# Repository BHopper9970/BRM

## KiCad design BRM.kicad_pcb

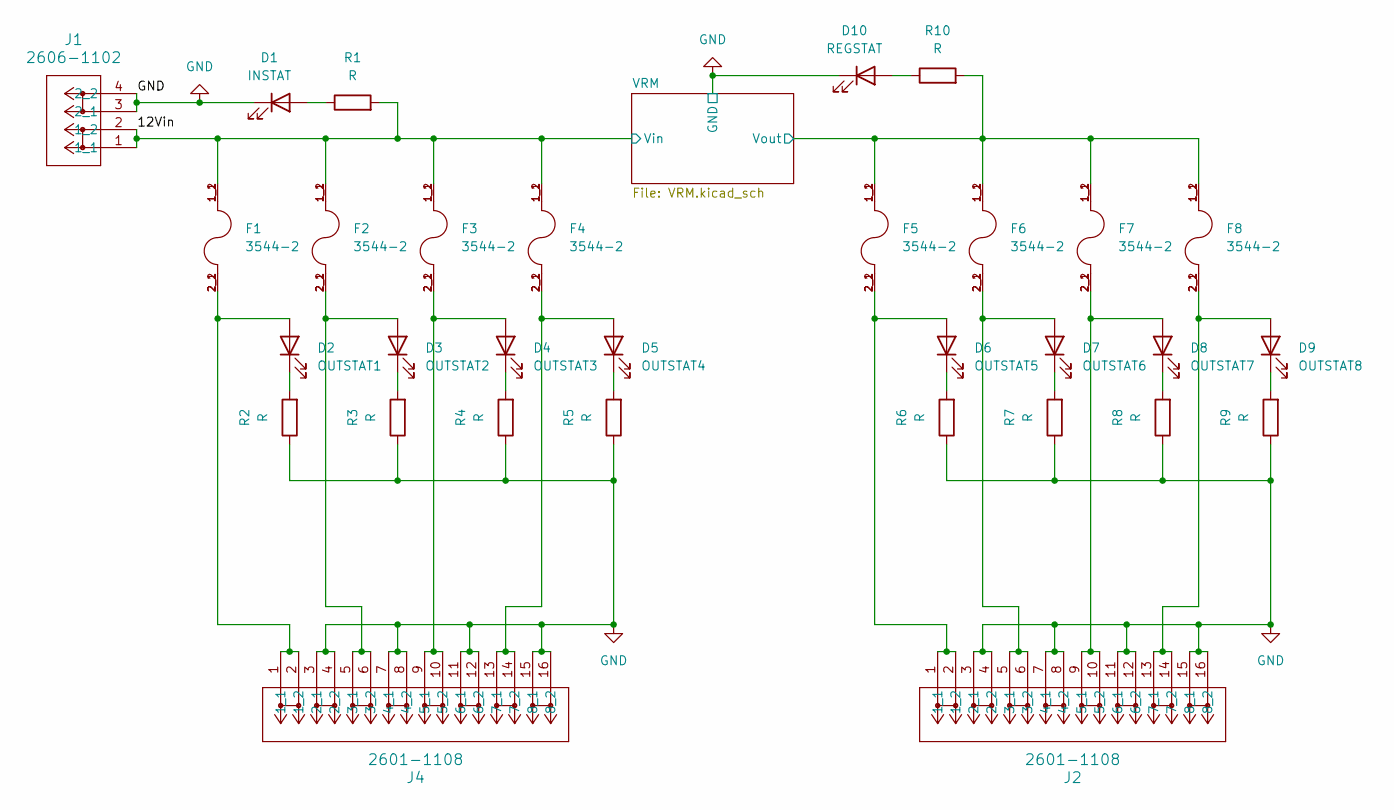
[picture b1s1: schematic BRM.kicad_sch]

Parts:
D1: INSTAT; LED_0805_2012Metric
D2: OUTSTAT1; LED_0805_2012Metric
D3: OUTSTAT2; LED_0805_2012Metric
D4: OUTSTAT3; LED_0805_2012Metric
D5: OUTSTAT4; LED_0805_2012Metric
D6: OUTSTAT5; LED_0805_2012Metric
D7: OUTSTAT6; LED_0805_2012Metric
D8: OUTSTAT7; LED_0805_2012Metric
D9: OUTSTAT8; LED_0805_2012Metric
D10: REGSTAT; LED_0805_2012Metric
F1, F2, F3, F4, F5, F6, F7, F8: 3544-2; FUSE_3544-2; PARTREV C
J1: 2606-1102; CONN2_2606-1102_WAG
J2, J4: 2601-1108; CONN8_2601-1108_WAG
R1, R2, R3, R4, R5, R6, R7, R8, R9, R10: R; R_0603_1608Metric

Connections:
/12Vin: F1.1_1, F1.1_2, F2.1_1, F2.1_2, F3.1_1, F3.1_2, F4.1_1, F4.1_2, J1.1 (1_1), J1.2 (1_2), R1.2; also elsewhere on the board
/VRM/Vout: F5.1_1, F5.1_2, F6.1_1, F6.1_2, F7.1_1, F7.1_2, F8.1_1, F8.1_2, R10.2; also elsewhere on the board
GND: D1.1 (K), D10.1 (K), J1.3 (2_1), J1.4 (2_2), J2.3 (2_1), J2.4 (2_2), J2.7 (4_1), J2.8 (4_2), J2.11 (6_1), J2.12 (6_2), J2.15 (8_1), J2.16 (8_2), J4.3 (2_1), J4.4 (2_2), J4.7 (4_1), J4.8 (4_2), J4.11 (6_1), J4.12 (6_2), J4.15 (8_1), J4.16 (8_2), R2.1, R3.1, R4.1, R5.1, R6.1, R7.1, R8.1, R9.1; also elsewhere on the board
unnamed: D1.2 (A), R1.1
unnamed: D2.2 (A), F1.2_1, F1.2_2, J4.1 (1_1), J4.2 (1_2)
unnamed: D2.1 (K), R2.2
unnamed: D3.2 (A), F2.2_1, F2.2_2, J4.5 (3_1), J4.6 (3_2)
unnamed: D3.1 (K), R3.2
unnamed: D4.2 (A), F3.2_1, F3.2_2, J4.9 (5_1), J4.10 (5_2)
unnamed: D4.1 (K), R4.2
unnamed: D5.2 (A), F4.2_1, F4.2_2, J4.13 (7_1), J4.14 (7_2)
unnamed: D5.1 (K), R5.2
unnamed: D6.2 (A), F5.2_1, F5.2_2, J2.1 (1_1), J2.2 (1_2)
unnamed: D6.1 (K), R6.2
unnamed: D7.2 (A), F6.2_1, F6.2_2, J2.5 (3_1), J2.6 (3_2)
unnamed: D7.1 (K), R7.2
unnamed: D8.2 (A), F7.2_1, F7.2_2, J2.9 (5_1), J2.10 (5_2)
unnamed: D8.1 (K), R8.2
unnamed: D9.2 (A), F8.2_1, F8.2_2, J2.13 (7_1), J2.14 (7_2)
unnamed: D9.1 (K), R9.2
unnamed: D10.2 (A), R10.1

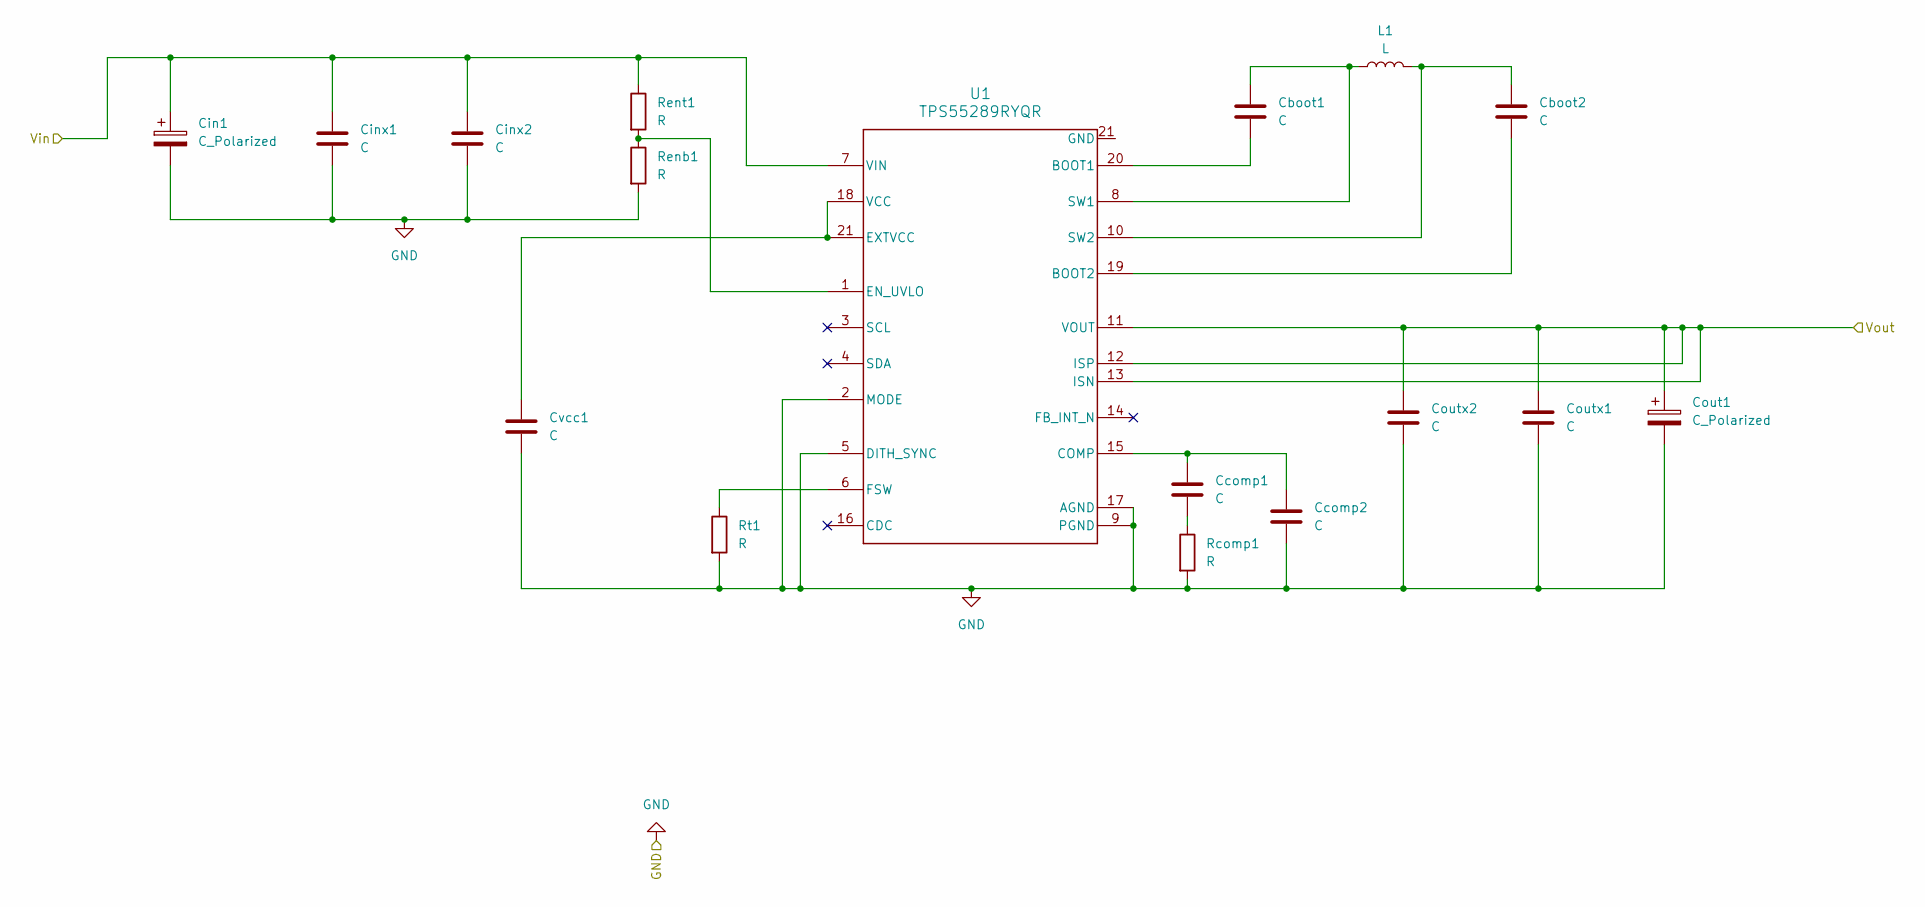
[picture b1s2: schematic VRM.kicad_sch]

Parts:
Cboot1, Cboot2: C; R_0603_1608Metric
Ccomp1, Ccomp2: C; C_0402_1005Metric
Cin1: C_Polarized; CP_Elec_8x6.9
Cinx1: C; C_1210_3225Metric
Cinx2: C; C_0402_1005Metric
Cout1: C_Polarized; CP_Elec_5x5.3
Coutx1: C; C_1206_3216Metric
Coutx2: C; C_0402_1005Metric
Cvcc1: C; C_0603_1608Metric
L1: L; L_Coilcraft_MSS1210-XXX
Rcomp1: R; R_0402_1005Metric
Renb1: R; R_0402_1005Metric
Rent1: R; R_0402_1005Metric
Rt1: R; R_0402_1005Metric
U1: TPS55289RYQR; RYQ0021A-MFG

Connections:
/12Vin: Cin1.1, Cinx1.1, Cinx2.1, Rent1.1, U1.7 (VIN); also elsewhere on the board
/VRM/Vout: Cout1.1, Coutx1.1, Coutx2.1, U1.11 (VOUT), U1.12 (ISP), U1.13 (ISN); also elsewhere on the board
GND: Ccomp2.2, Cin1.2, Cinx1.2, Cinx2.2, Cout1.2, Coutx1.2, Coutx2.2, Cvcc1.2, Rcomp1.2, Renb1.2, Rt1.2, U1.2 (MODE), U1.5 (DITH_SYNC), U1.9 (PGND), U1.17 (AGND); also elsewhere on the board
unnamed: Ccomp1.2, Rcomp1.1
unnamed: Cboot1.2, U1.20 (BOOT1)
unnamed: Cboot2.2, U1.19 (BOOT2)
unnamed: Ccomp1.1, Ccomp2.1, U1.15 (COMP)
unnamed: Renb1.1, Rent1.2, U1.1 (EN_UVLO)
unnamed: Cvcc1.1, U1.18 (VCC), U1.21 (EXTVCC)
unnamed: Rt1.1, U1.6 (FSW)
unnamed: Cboot1.1, L1.1, U1.8 (SW1)
unnamed: Cboot2.1, L1.2, U1.10 (SW2)

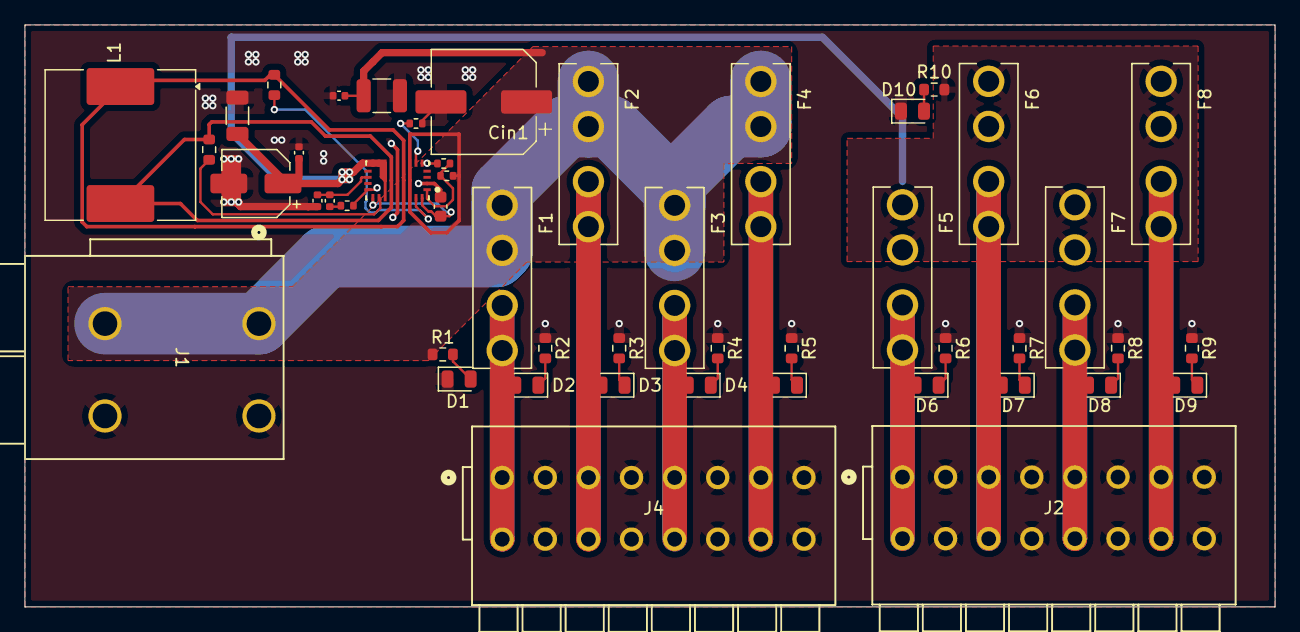
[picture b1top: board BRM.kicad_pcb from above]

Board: 2 copper layers, 101.5 x 47.2 mm, 48 parts (0 on the bottom side), 30 nets.

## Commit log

2026-01-30 initial commit, most of board already done
2026-01-30 Delete BRM-altium-import.kicad_sym
    some crap from an inital attempt
2026-01-30 PCB layout and VRM work
2026-01-30 VRM work
2026-01-31 DRC fixes and routing improvements
